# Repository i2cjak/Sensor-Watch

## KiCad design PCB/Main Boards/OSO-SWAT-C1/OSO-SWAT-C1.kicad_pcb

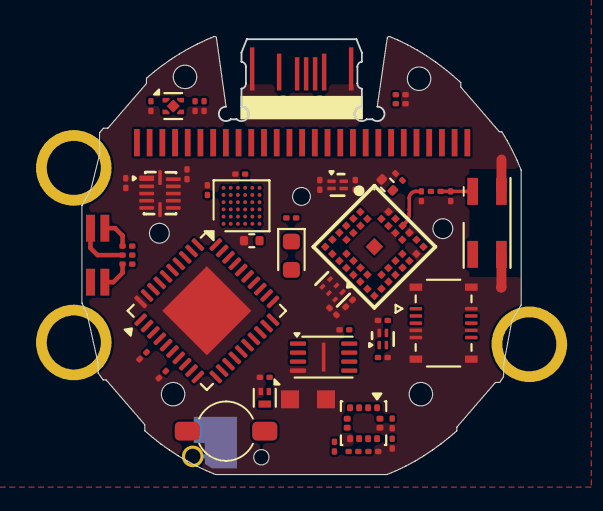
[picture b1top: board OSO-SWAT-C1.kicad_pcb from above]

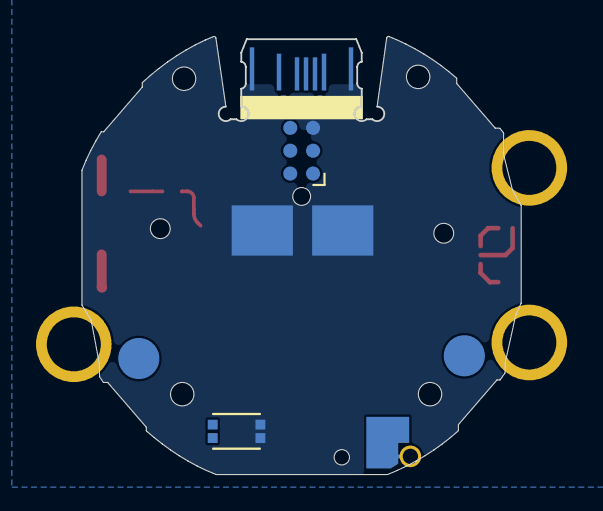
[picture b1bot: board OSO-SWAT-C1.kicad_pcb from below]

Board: 4 copper layers, 24.4 x 24.3 mm, 55 parts (2 on the bottom side), 78 nets.

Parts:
AE1: amemb-2450AT42E0100
BZ1: Buzzer; ELT3KN
C1, C2: TBD; C_0201_0603Metric_L
C3: 220nF; C_0201_0603Metric_L
C4, C5, C7, C8, C9, C10, C11, C12, C13, C14, C16, C17, C46, C47, C48, C49, C50, C51: 1uF; C_0201_0603Metric_L
C6, C15: 10uF; C_0402_1005Metric_L
D2: QBLP655-RGB; LED_QBLP655_RGB
J3: Conn_ARM_SWD_TagConnect_TC2030-NL; Tag-Connect_TC2030-IDC-NL_2x03_P1.27mm_Vertical
J4: Conn_02x05_Odd_Even_MountingPin; Hirose_DF40B-10DS-0.4V_2x05-1MP_P0.4mm
L1: 0R; R_0201_0603Metric_L
Q1: Q_Photo_NPN; D_0603_1608Metric
Q2: Q_NMOS_GSD; Diodes_DFN1006-3
R1: 10kR; R_0201_0603Metric_L
R3: 100kR, 0.1%; R_0201_0603Metric_L
R4, R6: 100R; R_0201_0603Metric_L
R5: 1kR; R_0201_0603Metric_L
R7, R8: 5.1kR; R_0201_0603Metric_L
R9, R10: 100kR; R_0201_0603Metric_L
RESET0: EVP-BB1AAB000; SW_EVP-BB1AAB000
TH1: 100kR; R_0201_0603Metric_L
TP1, TP2: TestPoint; TestPoint_Pad_1.0x1.0mm_No_Silk
U1: NCP115AMX250TCG; OnSemi_XDFN4-1EP_1.0x1.0mm_EP0.52x0.52mm
U2: ADXL367; amemb-ADXL367_LGA-12_2.11x2.21mm_P0.5mm_LayoutBorder2x4y
U3: HJ-N54L_SIP; COMM-SMD_L4.5-W4.5-P0.55-S0.55-TR
U4: BU97930MUV-E2; VQFN-40-1EP_6x6mm_P0.5mm_EP3.5x3.5mm
U5: W25Q128JVE; Winbond_USON-8-1EP_3x2mm_P0.5mm_EP0.2x1.6mm
U6, U10: TPS22991; 4-UQFN-0.9x0.8mm
U7: STM32L052T8Yx; ST_WLCSP-36_Die417
U8: TXU0204RUTR; UQFN-12_L2.0-W1.7-P0.40-TL
U9: TXU0101DRYR; SON-6_L1.5-W1.0-P0.50-TL
U$2: SENSOR-WATCH-USB; CASIO-F91W-OUTLINE-USB

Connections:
/ALARM: U3.1 (P0.00), U$2.ALARM
/BUZZER: Q2.1 (G), R9.1, U3.7 (P1.07)
/BUZZER_HV: BZ1.2 (-), Q2.3 (D), U$2.BUZZER
/COM0: U4.8 (COM0), U$2.7
/COM1: U4.9 (COM1), U$2.8
/COM2: U4.10 (COM2), U$2.9
/DBG_VDD: C49.1, C50.1, U8.1 (VCCA), U8.12 (OE), U9.1 (VCCA), U10.2 (ON)
/DEBUG.RX: U3.21 (P2.07), U7.F5 (USART2_RX)
/DEBUG.TX: U3.16 (P2.08), U7.E5 (USART2_TX)
/EN.EXT: U3.26 (P0.03), U6.2 (ON)
/GPIO.EXT: J4.10, U3.31 (P1.15)
/LEVEL_SHIFT_VDD: C47.1, C48.1, C51.1, U8.11 (VCCB), U9.6 (VCCB), U10.3 (VOUT)
/LIGHT: U3.27 (P0.01), U$2.LIGHT
/LIGHTSENSE: Q1.1 (C), R1.2
/MODE: U3.40 (P0.02), U$2.MODE
/MOSI: U3.36 (P1.09), U4.3 (MOSI)
/PDM.CLK: J4.4, U3.15 (P1.11)
/PDM.DIN: J4.6, U3.32 (P1.14)
/QSPI.D0: U3.13 (P2.02), U5.5 (DI/IO_{0})
/QSPI.D1: U3.38 (P2.04), U5.2 (DO/IO_{1})
/QSPI.D2: U3.35 (P2.03), U5.3 (~WP/IO_{2})
/QSPI.D3: U3.5 (P2.00), U5.7 (~HOLD/~RESET/IO_{3})
/QSPI.SCK: U3.6 (P2.01), U5.6 (CLK)
/QSPI.~CS: U3.4 (P2.05), U5.1 (~CS)
/SCK: U3.10 (P1.08), U4.2 (SCK)
/SCL: J4.3, U3.17 (P1.12)
/SDA: J4.5, U3.14 (P1.13)
/SEG0: U4.12 (SEG0), U$2.27
/SEG1: U4.13 (SEG1), U$2.26
/SEG2: U4.14 (SEG2), U$2.25
/SEG3: U4.15 (SEG3), U$2.24
/SEG4: U4.16 (SEG4), U$2.23
/SEG5: U4.17 (SEG5), U$2.22
/SEG6: U4.18 (SEG6), U$2.21
/SEG7: U4.19 (SEG7), U$2.20
/SEG8: U4.20 (SEG8), U$2.19
/SEG9: U4.21 (SEG9), U$2.18
/SEG10: U4.22 (SEG10), U$2.17
/SEG11: U4.23 (SEG11), U$2.16
/SEG12: U4.24 (SEG12), U$2.15
/SEG13: U4.25 (SEG13), U$2.14
/SEG14: U4.26 (SEG14), U$2.13
/SEG15: U4.27 (SEG15), U$2.12
/SEG16: U4.28 (SEG16), U$2.11
/SEG17: U4.29 (SEG17), U$2.10
/SEG18: U4.30 (SEG18), U$2.6
/SEG19: U4.31 (SEG19), U$2.5
/SEG20: U4.32 (SEG20), U$2.4
/SEG21: U4.33 (SEG21), U$2.3
/SEG22: U4.34 (SEG22), U$2.2
/SEG23: U4.35 (SEG23), U$2.1
/TARGET_SWDIO: U8.7 (B4), U9.4 (BY)
/TEMPSENSE: R3.1, TH1.2, U2.8 (ADC_{IN})
/~BLUE: R4.2, U3.9 (P1.06)
/~CS: U3.18 (P1.10), U4.1 (~CS)
/~GREEN: R5.2, U3.11 (P1.05)
/~LS_ENABLE: Q1.2 (E), U3.41 (P2.09)
/~RED: R6.2, U3.33 (P1.04)
/~RESET: J3.3 (~RESET), RESET0.B1, RESET0.B2, U3.37 (~RESET)
/~TS_ENABLE: R3.2, U3.3 (P2.10)
GND: AE1.3 (GND), AE1.4 (GND), C1.2, C2.2, C3.2, C4.2, C5.2, C6.2, C7.2, C8.2, C9.2, C10.2, C11.2, C12.2, C13.2, C14.2, C15.2, C16.2, C17.2, C46.2, C47.2, C48.2, C49.2, C50.2, C51.2, J3.5 (GND), J4.2, J4.7, J4.8, J4.9, J4.MP (MountPin), Q2.2 (S), R7.1, R8.1, R9.2, R10.2, RESET0.A1, RESET0.A2, U1.2 (GND), U1.5 (GND), U2.7 (GND), U2.11 (GND), U3.19 (GND), U3.22 (GND), U3.25 (GND), U3.39 (GND), U4.40 (VSS), U4.41 (VSS), U5.4 (GND), U5.9 (EP), U6.4 (GND), U7.D6 (VSS), U8.6 (GND), U9.2 (GND), U10.4 (GND), U$2.GND, U$2.GND1, U$2.GND2
unnamed: AE1.1 (FEED), C2.1, L1.2
unnamed: D2.1 (CR), R6.1
unnamed: D2.4 (CG), R5.1
unnamed: D2.3 (CB), R4.1
unnamed: J3.4 (SWCLK), U3.28 (SWDCLK)
unnamed: J3.2 (SWDIO), U3.2 (SWDIO)
unnamed: C13.1, J4.1, U6.3 (VOUT)
unnamed: R7.2, U$2.CC1
unnamed: R8.2, U$2.CC2
unnamed: C9.1, C15.1, C16.1, C17.1, U1.1 (OUT), U7.A5 (VDD), U7.D5 (VDDA), U7.F1 (VDD)
unnamed: C3.1, U2.9 (V_{REG_OUT})
unnamed: TP1.1 (1_1), U3.8 (P1.02)
unnamed: TP2.1 (1_1), U3.30 (P1.03)
unnamed: C1.1, L1.1, U3.23 (RF)
VBUS: C8.1, R10.1, U1.3 (EN), U1.4 (IN), U$2.VBUS
VDD: BZ1.1 (+), C4.1, C5.1, C6.1, C7.1, C10.1, C11.1, C12.1, C14.1, D2.2 (A), J3.1 (VCC), R1.1, TH1.1, U2.10 (V_{S}), U2.12 (V_{DDIO}), U3.42 (VDD), U4.4 (VDD), U4.7 (VLCD), U5.8 (VCC), U6.1 (VIN), U$2.VCC1, U$2.VCC2
VDD_nRF: C46.1, U10.1 (VIN)

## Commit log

2026-06-11 Initial commit.
